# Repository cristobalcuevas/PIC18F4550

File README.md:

# PIC18F4550
Codes for PIC18F4550

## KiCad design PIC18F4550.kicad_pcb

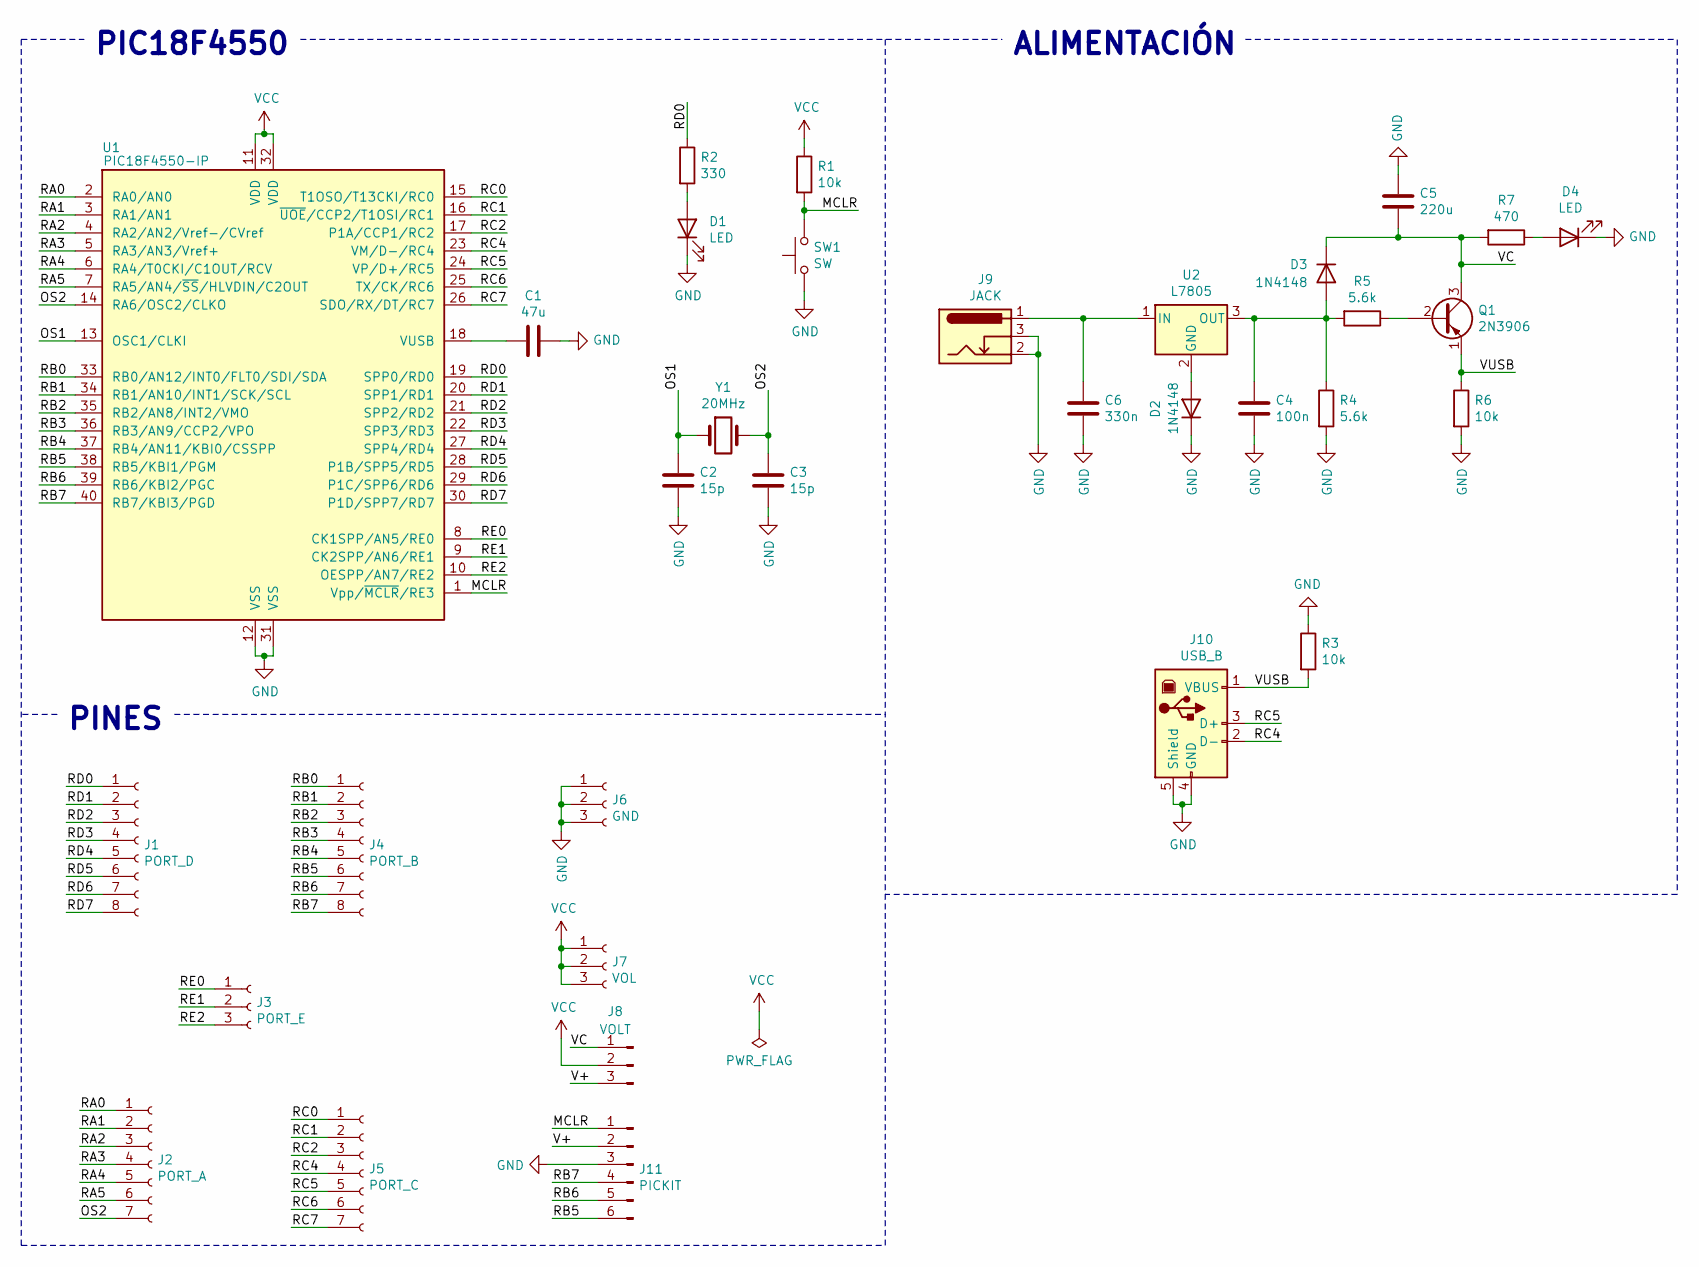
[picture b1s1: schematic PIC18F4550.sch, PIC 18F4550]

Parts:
C1: 47u; CP_Radial_D6.3mm_P2.50mm
C2, C3: 15p; C_Disc_D3.8mm_W2.6mm_P2.50mm
C4: 100n; C_Disc_D3.8mm_W2.6mm_P2.50mm
C5: 220u; CP_Radial_D10.0mm_P2.50mm
C6: 330n; C_Disc_D3.8mm_W2.6mm_P2.50mm
D1, D4: LED; LED_D5.0mm
D2, D3: 1N4148; D_DO-35_SOD27_P7.62mm_Horizontal
J1: PORT_D; PinSocket_1x08_P2.54mm_Vertical
J2: PORT_A; PinSocket_1x07_P2.54mm_Vertical
J3: PORT_E; PinSocket_1x03_P2.54mm_Vertical
J4: PORT_B; PinSocket_1x08_P2.54mm_Vertical
J5: PORT_C; PinSocket_1x07_P2.54mm_Vertical
J6: GND; PinSocket_1x03_P2.54mm_Vertical
J7: VOL; PinSocket_1x03_P2.54mm_Vertical
J8: VOLT; PinHeader_1x03_P2.54mm_Vertical
J9: JACK; BarrelJack_Horizontal
J10: USB_B; USB_B_OST_USB-B1HSxx_Horizontal
J11: PICKIT; PinHeader_1x06_P2.54mm_Vertical
Q1: 2N3906; TO-92_Inline
R1, R3, R6: 10k; R_Axial_DIN0207_L6.3mm_D2.5mm_P7.62mm_Horizontal
R2: 330; R_Axial_DIN0207_L6.3mm_D2.5mm_P7.62mm_Horizontal
R4, R5: 5.6k; R_Axial_DIN0207_L6.3mm_D2.5mm_P7.62mm_Horizontal
R7: 470; R_Axial_DIN0207_L6.3mm_D2.5mm_P7.62mm_Horizontal
SW1: SW; SW_PUSH_6mm
U1: PIC18F4550-IP; DIP-40_W15.24mm
U2: L7805; TO-220-3_Vertical
Y1: 20MHz; Crystal_HC50_Vertical

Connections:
/MCLR: J11.1, R1.2, SW1.2, U1.1 (Vpp/~MCLR~/RE3)
/OS1: C2.1, U1.13 (OSC1/CLKI), Y1.1
/OS2: C3.1, J2.7, U1.14 (RA6/OSC2/CLKO), Y1.2
/RA0: J2.1, U1.2 (RA0/AN0)
/RA1: J2.2, U1.3 (RA1/AN1)
/RA2: J2.3, U1.4 (RA2/AN2/Vref-/CVref)
/RA3: J2.4, U1.5 (RA3/AN3/Vref+)
/RA4: J2.5, U1.6 (RA4/T0CKI/C1OUT/RCV)
/RA5: J2.6, U1.7 (RA5/AN4/~SS~/HLVDIN/C2OUT)
/RB0: J4.1, U1.33 (RB0/AN12/INT0/FLT0/SDI/SDA)
/RB1: J4.2, U1.34 (RB1/AN10/INT1/SCK/SCL)
/RB2: J4.3, U1.35 (RB2/AN8/INT2/VMO)
/RB3: J4.4, U1.36 (RB3/AN9/CCP2/VPO)
/RB4: J4.5, U1.37 (RB4/AN11/KBI0/CSSPP)
/RB5: J4.6, J11.6, U1.38 (RB5/KBI1/PGM)
/RB6: J4.7, J11.5, U1.39 (RB6/KBI2/PGC)
/RB7: J4.8, J11.4, U1.40 (RB7/KBI3/PGD)
/RC0: J5.1, U1.15 (T1OSO/T13CKI/RC0)
/RC1: J5.2, U1.16 (~UOE~/CCP2/T1OSI/RC1)
/RC2: J5.3, U1.17 (P1A/CCP1/RC2)
/RC4: J5.4, J10.2 (D-), U1.23 (VM/D-/RC4)
/RC5: J5.5, J10.3 (D+), U1.24 (VP/D+/RC5)
/RC6: J5.6, U1.25 (TX/CK/RC6)
/RC7: J5.7, U1.26 (SDO/RX/DT/RC7)
/RD0: J1.1, R2.1, U1.19 (SPP0/RD0)
/RD1: J1.2, U1.20 (SPP1/RD1)
/RD2: J1.3, U1.21 (SPP2/RD2)
/RD3: J1.4, U1.22 (SPP3/RD3)
/RD4: J1.5, U1.27 (SPP4/RD4)
/RD5: J1.6, U1.28 (P1B/SPP5/RD5)
/RD6: J1.7, U1.29 (P1C/SPP6/RD6)
/RD7: J1.8, U1.30 (P1D/SPP7/RD7)
/RE0: J3.1, U1.8 (CK1SPP/AN5/RE0)
/RE1: J3.2, U1.9 (CK2SPP/AN6/RE1)
/RE2: J3.3, U1.10 (OESPP/AN7/RE2)
/V+: J8.3, J11.2
/VC: C5.2, D3.1 (K), J8.1, Q1.3 (C), R7.2
/VUSB: J10.1 (VBUS), Q1.1 (E), R3.2, R6.1
GND: C1.1, C2.2, C3.2, C4.2, C5.1, C6.2, D1.1 (K), D2.1 (K), D4.1 (K), J6.1, J6.2, J6.3, J9.2, J9.3, J10.4 (GND), J10.5 (Shield), J11.3, R3.1, R4.2, R6.2, SW1.1, U1.12 (VSS), U1.31 (VSS)
unnamed: C1.2, U1.18 (VUSB)
unnamed: C4.1, D3.2 (A), R4.1, R5.2, U2.3 (OUT)
unnamed: C6.1, J9.1, U2.1 (IN)
unnamed: D1.2 (A), R2.2
unnamed: D2.2 (A), U2.2 (GND)
unnamed: D4.2 (A), R7.1
unnamed: Q1.2 (B), R5.1
VCC: J7.1, J7.2, J7.3, J8.2, R1.1, U1.11 (VDD), U1.32 (VDD)

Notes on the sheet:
PIC18F4550
PINES
ALIMENTACIÓN

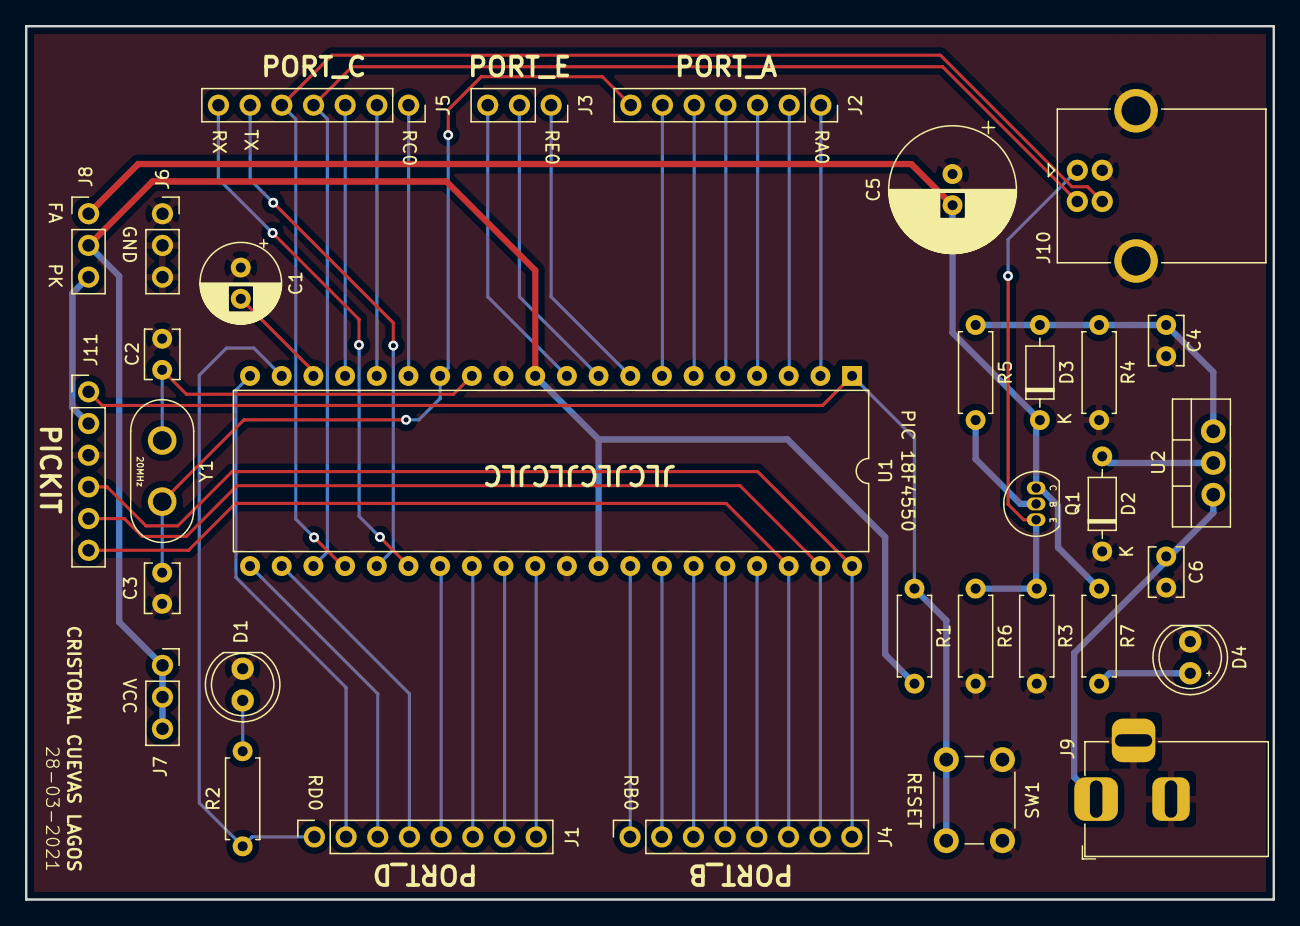
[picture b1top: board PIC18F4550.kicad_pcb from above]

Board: 2 copper layers, 100.0 x 70.0 mm, 33 parts (0 on the bottom side), 47 nets.

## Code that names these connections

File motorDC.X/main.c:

/*
 * File:   main.c
 * Author: Cristobal
 *
 * Created on 4 de abril de 2021, 15:19
 */

#include <xc.h>
#include "configuracion.h"

void main(void) {
    TRISDbits.RD0 = 0; // Solo RA0 es salida
    TRISDbits.RD1 = 0; // Solo RB0 es salida
    TRISDbits.RD2 = 0; // Solo RC0 es salida
    LATDbits.LATD2 = 1;
    while(1){
        LATDbits.LATD0 = 1;
        LATDbits.LATD1 = 0;
        __delay_ms(500);
        LATDbits.LATD0 = 0;
        LATDbits.LATD1 = 1;
        __delay_ms(500);
        LATDbits.LATD0 = 1;
        LATDbits.LATD1 = 1;
        __delay_ms(500);
    }
    return;
}

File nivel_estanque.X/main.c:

/*
 * File:   main.c
 * Author: Cristobal
 *
 * Created on 25 de agosto de 2021, 13:49
 */

#include <xc.h>
#include "configuracion.h"

enum Estado {BOMBA_1, LLENADO, BOMBA_2} estado;

void main(void) {
    // RB0 y RB1 como salidas que corresponden a las bombas
    TRISBbits.RB0 = 0;
    TRISBbits.RB1 = 0;
    // RB2, RB3 y RB4 como salidas que corresponden a los leds de aviso
    TRISBbits.RB2 = 0;
    TRISBbits.RB3 = 0;
    TRISBbits.RB4 = 0;
    // RD3 como entrada que corresponde al interruptor de nivel
    TRISDbits.RD3 = 1;
    // Estado inicial
    estado = LLENADO;
    // Variable de estado
    uint8_t estadoActual = 0;
    while(1){
        switch(estado){
            case LLENADO:
                LATBbits.LATB0 = 0; // Bomba 1 apagada
                LATBbits.LATB1 = 0; // Bomba 2 apagada
                LATBbits.LATB2 = 0; // Led Bomba 1 apagado
                LATBbits.LATB3 = 0; // Led Bomba 1 apagado
                LATBbits.LATB4 = 1; // Led Llenado encendido
                if(PORTDbits.RD3 == 1 && estadoActual == 0){
                    estado = BOMBA_1;
                }
                else if(PORTDbits.RD3 == 1 && estadoActual == 1){
                    estado = BOMBA_2;
                }
                break;
            case BOMBA_1:
                LATBbits.LATB0 = 1; // Bomba 1 encendida
                LATBbits.LATB1 = 0; // Bomba 2 apagada
                LATBbits.LATB2 = 1; // Led Bomba 1 encendido
                LATBbits.LATB4 = 0; // Led Llenado apagado
                if(PORTDbits.RD3 == 0){
                    estado = LLENADO;
                    estadoActual = 1;
                }
                break;
            case BOMBA_2:
                LATBbits.LATB0 = 0; // Bomba 1 apagada
                LATBbits.LATB1 = 1; // Bomba 2 encendida
                LATBbits.LATB3 = 1; // Led Bomba 2 encendido
                LATBbits.LATB4 = 0; // Led Llenado apagado
                if(PORTDbits.RD3 == 0){
                    estado = LLENADO;
                    estadoActual = 0;
                }
                break;
            default:
                estado = LLENADO;
                break;
        }
    }
    return;
}

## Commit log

2022-08-31 codes for pic18f4550
2022-10-12 update files
2022-10-12 add gitignore
